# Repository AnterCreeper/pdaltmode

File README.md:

# USB PD Alt-mode Host-side Negotiation

If any questions, welcome for Issues & PRs   
如果有疑问，欢迎提交Issues或PR

**WARNING! This Project is not been fully long-term productive tested and without warranty of any kind, use at your own risk!**   
**警告！该项目未经充分的长期生产环境测试，作者不作任何保证，使用需要你自己衡量**

### License

This project is licensed under the LGPL-2.1-or-later license. **DO NOT** download or clone this project until you have read and agree the LICENSE.     
该项目采用 `LGPL-2.1 以及之后版本` 授权。当你下载或克隆项目时，默认已经阅读并同意该协定。

### TODO

1. Active Cable Support (not in plan)
2. Audio Transmission Function Testing

### Overview

This Project is used to perform PD Logic for Host-side based on the cost-effective (30 cents at the time of writing) WCH CH32X035 32-bit RISC-V microcontroller, to achieve DisplayPort output over Type-C, which can be used on space compact scene.    
该项目基于来自 WCH 的低成本 CH32X035 微控制器，包含了所需的所有主机端的 USB Power Delivery 协议的功能，以实现 Type-C 上 DisplayPort 视频输出功能，可用于 PCB 面积紧凑场景。

Besides, This Project include a validation hardware with GERBER and schematics, 4 layers JLC04081H-3313 Stacking, using TOSHIBA TC358867XBG to convert Video stream from Parallel to DisplayPort Signal.   
此外，该项目附有一个验证硬件，包含 GERBER 和原理图与装配图纸，四层 0.8mm JLC04081H-3313 叠层，采用 TOSHIBA TC358867XBG 将 RGB 并行接口 转换至 DisplayPort 信号输出。

This Project implements state machines defined in:
1. Universal Serial Bus Power Delivery Specification Rev 2.0 Ver 1.3
2. Universal Serial Bus Type-C Cable and Connector Specification Ver 2.2.
3. VESA DisplayPort Alt Mode on USB Type-C Standard. Ver 1.3/1.4.
4. VESA DisplayPort Standard. Version 1, Revision 2.

Doc. 1 and 2 can be accessed from https://github.com/usb-c/USB-Type-C   
For Doc. 3, since **DISTRIBUTION TO NON-MEMBERS IS PROHIBITED**, contact me at [wangzhihao9@hotmail.com](mailto:wangzhihao9@hotmail.com)  
Doc.4 is located at https://glenwing.github.io/docs/DP-1.2.pdf

Datasheet of TC358867XBG is included in the project, which includes external LICENSE.

Some other Specification related to Audio which is needed: (May have copies over web.archive.org)
1. [CEA 861-E](https://members.cta.tech/ctaPublicationDetails/?id=95190170-1031-e811-bbd4-0003ff52999d): A DTV Profile for Uncompressed High Speed Digital Interfaces
2. [IEC60958](https://webstore.iec.ch/en/publication/62829): Digital Audio Interfaces

### Usage

1. Download and Open with MounRiver Studio II [Download Page](http://www.mounriver.com/download)
2. Connect the board with WCH Link-E, then Compile and Run
3. ~~Files except in User is remain unchanged from default.~~

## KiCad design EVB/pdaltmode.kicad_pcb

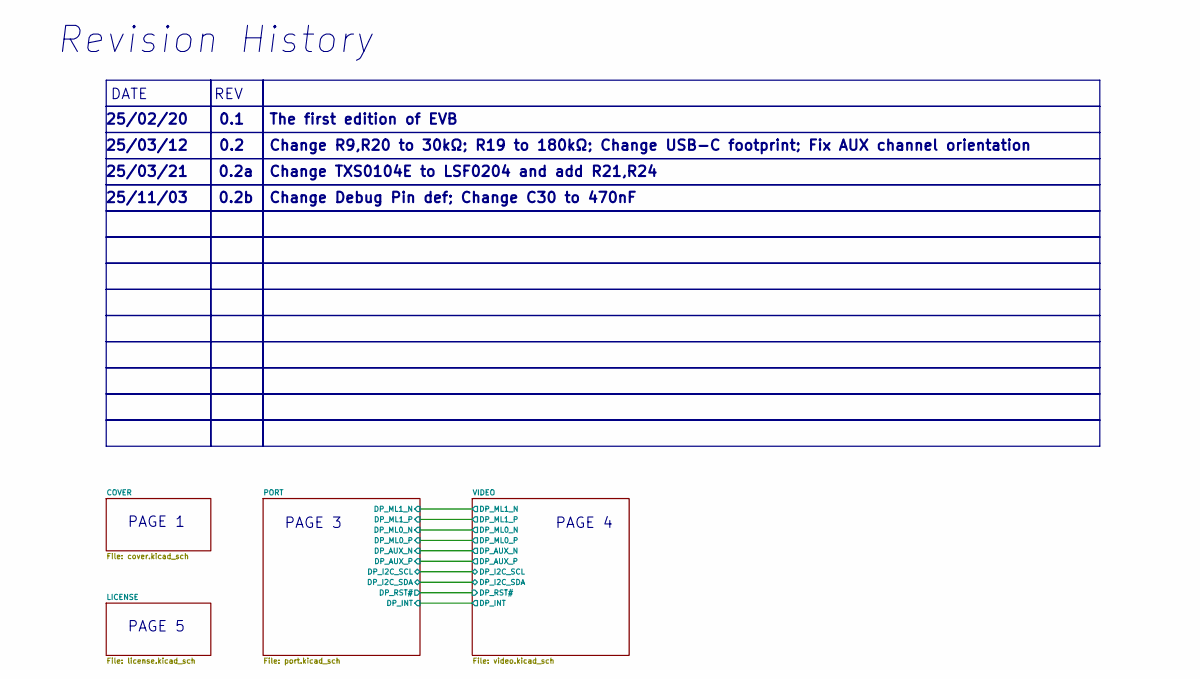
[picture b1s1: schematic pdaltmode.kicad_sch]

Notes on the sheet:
Change Debug Pin def; Change C30 to 470nF
Change TXS0104E to LSF0204 and add R21,R24
PAGE 5
25/11/03
PAGE 3
PAGE 1
0.2b
Change R9,R20 to 30kΩ; R19 to 180kΩ; Change USB-C footprint; Fix AUX channel orientation
0.1
Revision History
The first edition of EVB
DATE
25/03/12
0.2a
0.2
25/03/21
PAGE 4
REV
25/02/20

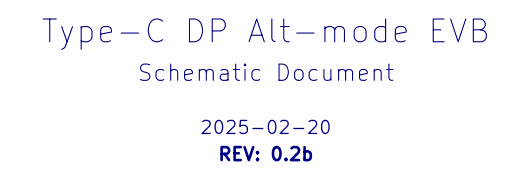
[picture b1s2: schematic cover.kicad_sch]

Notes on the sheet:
REV: 0.2b
2025-02-20
Type-C DP Alt-mode EVB
Schematic Document

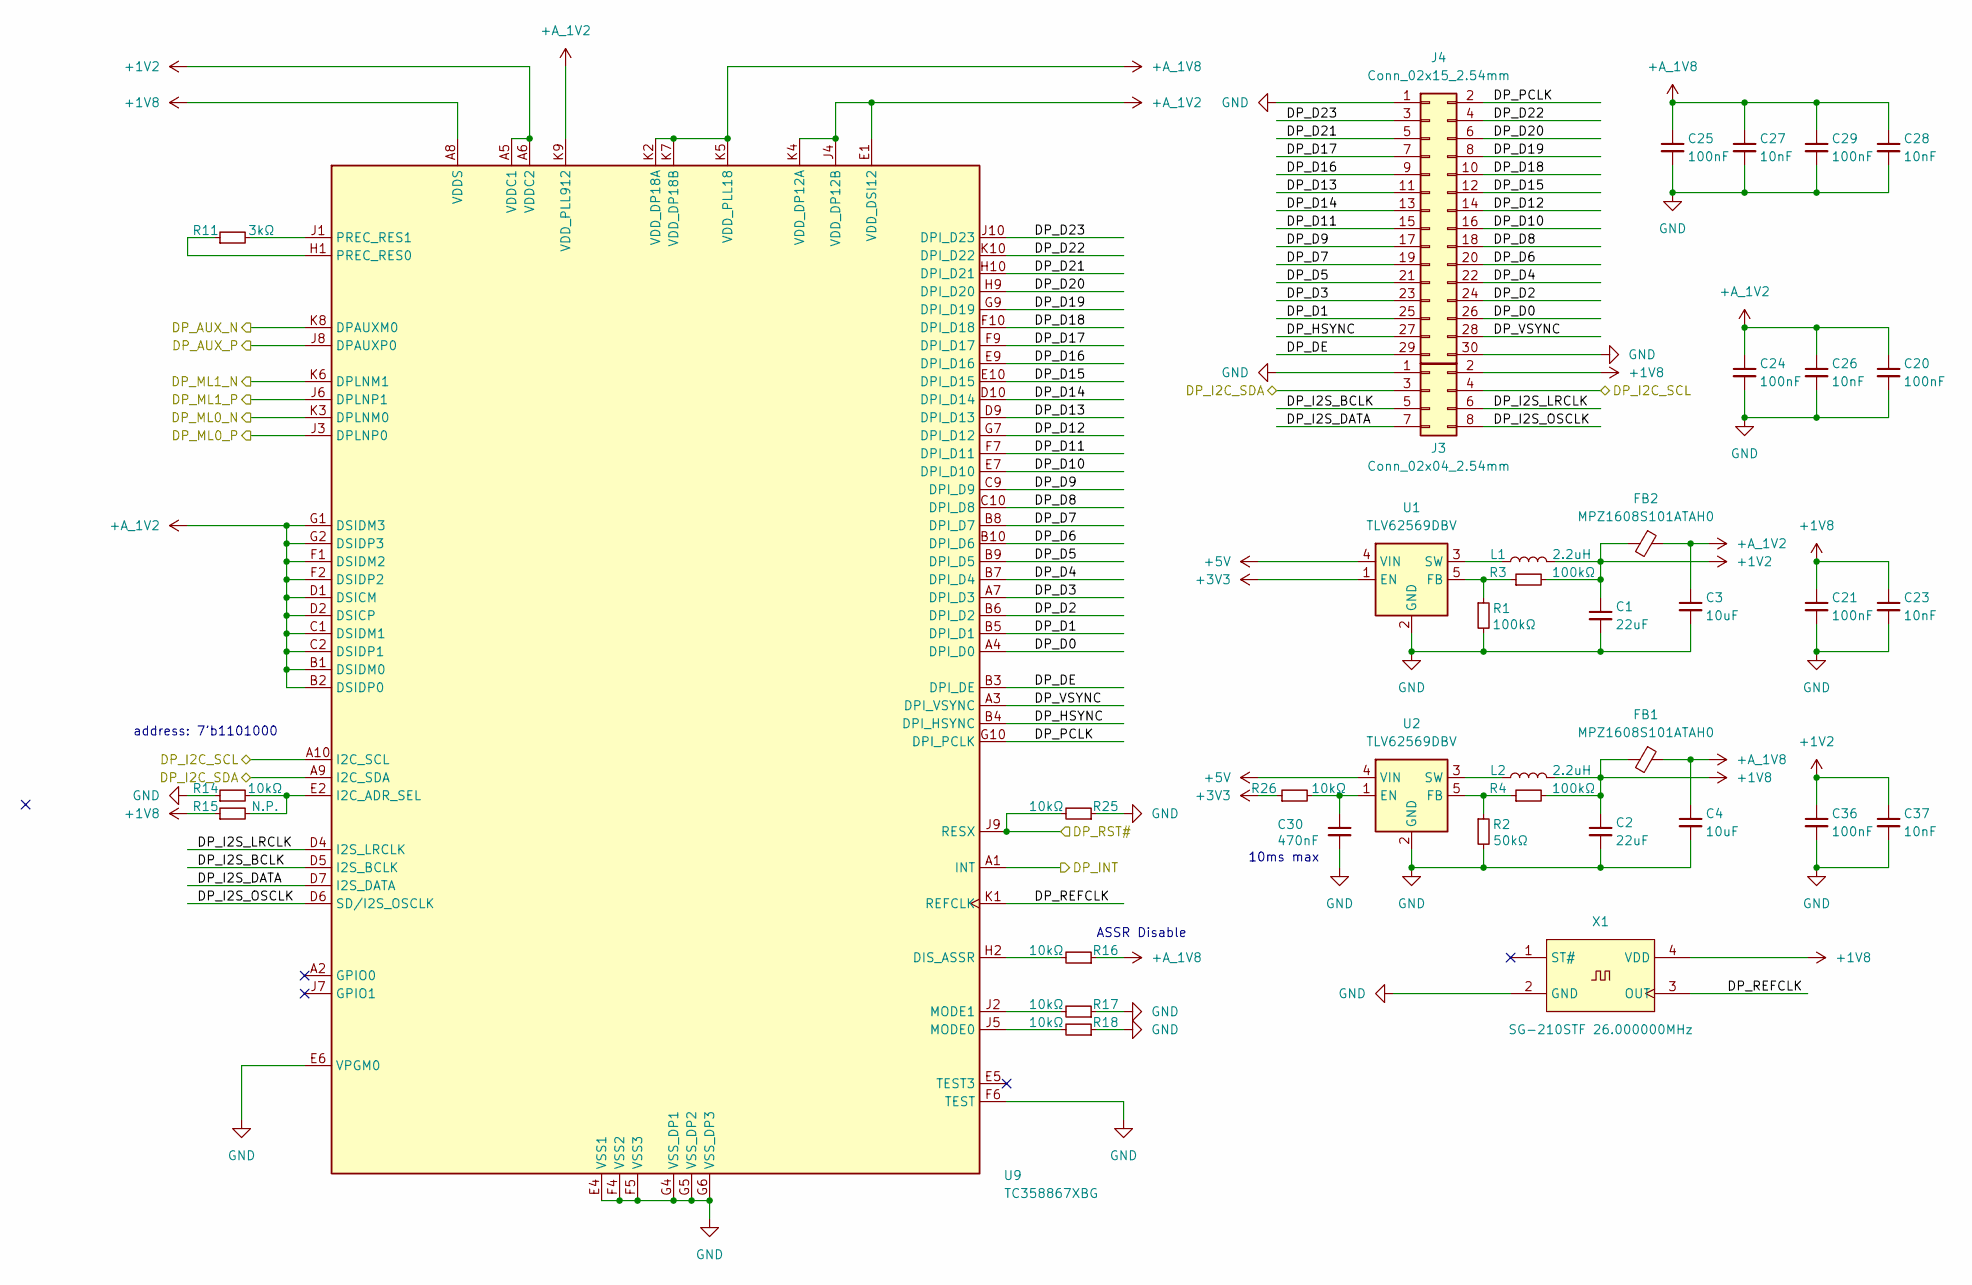
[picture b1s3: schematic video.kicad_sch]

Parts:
C1, C2: 22uF; C_0603_1608Metric
C3, C4: 10uF; C_0603_1608Metric
C20, C21, C24, C25, C29, C36: 100nF; C_0402_1005Metric
C23, C26, C27, C28, C37: 10nF; C_0402_1005Metric
C30: 470nF; C_0402_1005Metric
FB1, FB2: MPZ1608S101ATAH0; L_0603_1608Metric
J3: Conn_02x04_2.54mm; PinHeader_2x04_P2.54mm_Vertical
J4: Conn_02x15_2.54mm; PinHeader_2x15_P2.54mm_Vertical
L1, L2: 2.2uH; L_Murata_DFE201610P
R1, R3, R4: 100kΩ; R_0402_1005Metric
R2: 50kΩ; R_0402_1005Metric
R11: 3kΩ; R_0402_1005Metric
R14, R16, R17, R18, R25, R26: 10kΩ; R_0402_1005Metric
R15: N.P.; R_0402_1005Metric
U1, U2: TLV62569DBV; SOT-23-5
U9: TC358867XBG; Toshiba_VFBGA-80_7.0x7.0mm
X1: SG-210STF 26.000000MHz; Oscillator_SMD_SeikoEpson_SG210-4Pin_2.5x2.0mm

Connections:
+1V2: C1.1, C36.1, C37.1, FB2.2, L1.2, R3.2, U9.A5 (VDDC1), U9.A6 (VDDC2)
+1V8: C2.1, C21.1, C23.1, FB1.2, J3.2, L2.2, R4.2, R15.1, U9.A8 (VDDS), X1.4 (VDD); also elsewhere on the board
+3V3: R26.1, U1.1 (EN); also elsewhere on the board
+5V: U1.4 (VIN), U2.4 (VIN); also elsewhere on the board
+A_1V2: C3.1, C20.1, C24.1, C26.1, FB2.1, U9.B1 (DSIDM0), U9.B2 (DSIDP0), U9.C1 (DSIDM1), U9.C2 (DSIDP1), U9.D1 (DSICM), U9.D2 (DSICP), U9.E1 (VDD_DSI12), U9.F1 (DSIDM2), U9.F2 (DSIDP2), U9.G1 (DSIDM3), U9.G2 (DSIDP3), U9.J4 (VDD_DP12B), U9.K4 (VDD_DP12A), U9.K9 (VDD_PLL912)
+A_1V8: C4.1, C25.1, C27.1, C28.1, C29.1, FB1.1, R16.1, U9.K2 (VDD_DP18A), U9.K5 (VDD_PLL18), U9.K7 (VDD_DP18B)
/PORT/DP_AUX_N: U9.K8 (DPAUXM0); also elsewhere on the board
/PORT/DP_AUX_P: U9.J8 (DPAUXP0); also elsewhere on the board
/PORT/DP_I2C_SCL: J3.4, U9.A10 (I2C_SCL); also elsewhere on the board
/PORT/DP_I2C_SDA: J3.3, U9.A9 (I2C_SDA); also elsewhere on the board
/PORT/DP_INT: U9.A1 (INT); also elsewhere on the board
/PORT/DP_ML0_N: U9.K3 (DPLNM0); also elsewhere on the board
/PORT/DP_ML0_P: U9.J3 (DPLNP0); also elsewhere on the board
/PORT/DP_ML1_N: U9.K6 (DPLNM1); also elsewhere on the board
/PORT/DP_ML1_P: U9.J6 (DPLNP1); also elsewhere on the board
/PORT/DP_RST#: R25.2, U9.J9 (RESX); also elsewhere on the board
/VIDEO/DP_D0: J4.26, U9.A4 (DPI_D0)
/VIDEO/DP_D1: J4.25, U9.B5 (DPI_D1)
/VIDEO/DP_D2: J4.24, U9.B6 (DPI_D2)
/VIDEO/DP_D3: J4.23, U9.A7 (DPI_D3)
/VIDEO/DP_D4: J4.22, U9.B7 (DPI_D4)
/VIDEO/DP_D5: J4.21, U9.B9 (DPI_D5)
/VIDEO/DP_D6: J4.20, U9.B10 (DPI_D6)
/VIDEO/DP_D7: J4.19, U9.B8 (DPI_D7)
/VIDEO/DP_D8: J4.18, U9.C10 (DPI_D8)
/VIDEO/DP_D9: J4.17, U9.C9 (DPI_D9)
/VIDEO/DP_D10: J4.16, U9.E7 (DPI_D10)
/VIDEO/DP_D11: J4.15, U9.F7 (DPI_D11)
/VIDEO/DP_D12: J4.14, U9.G7 (DPI_D12)
/VIDEO/DP_D13: J4.11, U9.D9 (DPI_D13)
/VIDEO/DP_D14: J4.13, U9.D10 (DPI_D14)
/VIDEO/DP_D15: J4.12, U9.E10 (DPI_D15)
/VIDEO/DP_D16: J4.9, U9.E9 (DPI_D16)
/VIDEO/DP_D17: J4.7, U9.F9 (DPI_D17)
/VIDEO/DP_D18: J4.10, U9.F10 (DPI_D18)
/VIDEO/DP_D19: J4.8, U9.G9 (DPI_D19)
/VIDEO/DP_D20: J4.6, U9.H9 (DPI_D20)
/VIDEO/DP_D21: J4.5, U9.H10 (DPI_D21)
/VIDEO/DP_D22: J4.4, U9.K10 (DPI_D22)
/VIDEO/DP_D23: J4.3, U9.J10 (DPI_D23)
/VIDEO/DP_DE: J4.29, U9.B3 (DPI_DE)
/VIDEO/DP_HSYNC: J4.27, U9.B4 (DPI_HSYNC)
/VIDEO/DP_I2S_BCLK: J3.5, U9.D5 (I2S_BCLK)
/VIDEO/DP_I2S_DATA: J3.7, U9.D7 (I2S_DATA)
/VIDEO/DP_I2S_LRCLK: J3.6, U9.D4 (I2S_LRCLK)
/VIDEO/DP_I2S_OSCLK: J3.8, U9.D6 (SD/I2S_OSCLK)
/VIDEO/DP_PCLK: J4.2, U9.G10 (DPI_PCLK)
/VIDEO/DP_REFCLK: U9.K1 (REFCLK), X1.3 (OUT)
/VIDEO/DP_VSYNC: J4.28, U9.A3 (DPI_VSYNC)
GND: C1.2, C2.2, C3.2, C4.2, C20.2, C21.2, C23.2, C24.2, C25.2, C26.2, C27.2, C28.2, C29.2, C30.2, C36.2, C37.2, J3.1, J4.1, J4.30, R1.2, R2.2, R14.1, R17.1, R18.1, R25.1, U1.2 (GND), U2.2 (GND), U9.E4 (VSS1), U9.E6 (VPGM0), U9.F4 (VSS2), U9.F5 (VSS3), U9.F6 (TEST), U9.G4 (VSS_DP1), U9.G5 (VSS_DP2), U9.G6 (VSS_DP3), X1.2 (GND); also elsewhere on the board
unnamed: R1.1, R3.1, U1.5 (FB)
unnamed: L1.1, U1.3 (SW)
unnamed: C30.1, R26.2, U2.1 (EN)
unnamed: R2.1, R4.1, U2.5 (FB)
unnamed: L2.1, U2.3 (SW)
unnamed: R16.2, U9.H2 (DIS_ASSR)
unnamed: R14.2, R15.2, U9.E2 (I2C_ADR_SEL)
unnamed: R18.2, U9.J5 (MODE0)
unnamed: R17.2, U9.J2 (MODE1)
unnamed: R11.1, U9.H1 (PREC_RES0)
unnamed: R11.2, U9.J1 (PREC_RES1)

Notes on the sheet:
ASSR Disable
10ms max
address: 7'b1101000

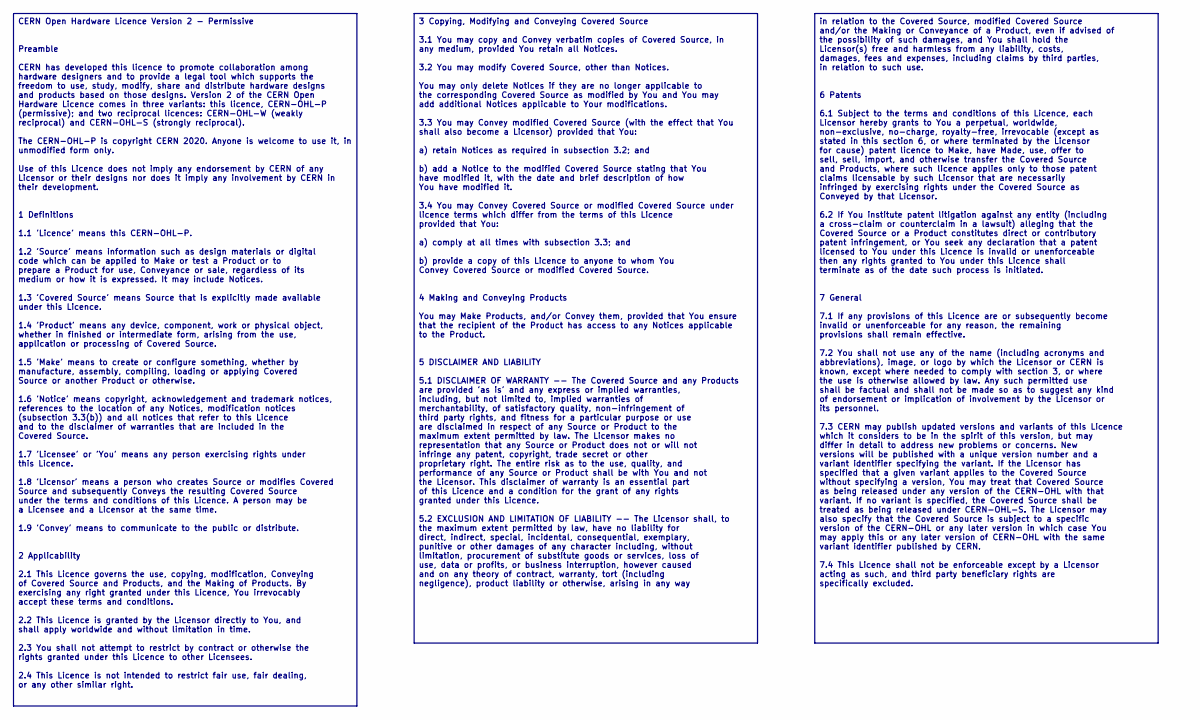
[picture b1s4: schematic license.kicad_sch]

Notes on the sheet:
3 Copying, Modifying and Conveying Covered Source 3.1 You may copy and Convey verbatim copies of Covered Source, in any medium, provided You retain all Notices. 3.2 You may modify Covered Source, other than Notices. You may only delete Notices if they are no longer applicable to the corresponding C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
CERN Open Hardware Licence Version 2 - Permissive Preamble CERN has developed this licence to promote collaboration among hardware designers and to provide a legal tool which supports the freedom to use, study, modify, share and distribute hardware designs and products based on those designs. Versi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
in relation to the Covered Source, modified Covered Source and/or the Making or Conveyance of a Product, even if advised of the possibility of such damages, and You shall hold the Licensor(s) free and harmless from any liability, costs, damages, fees and expenses, including claims by third parties,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

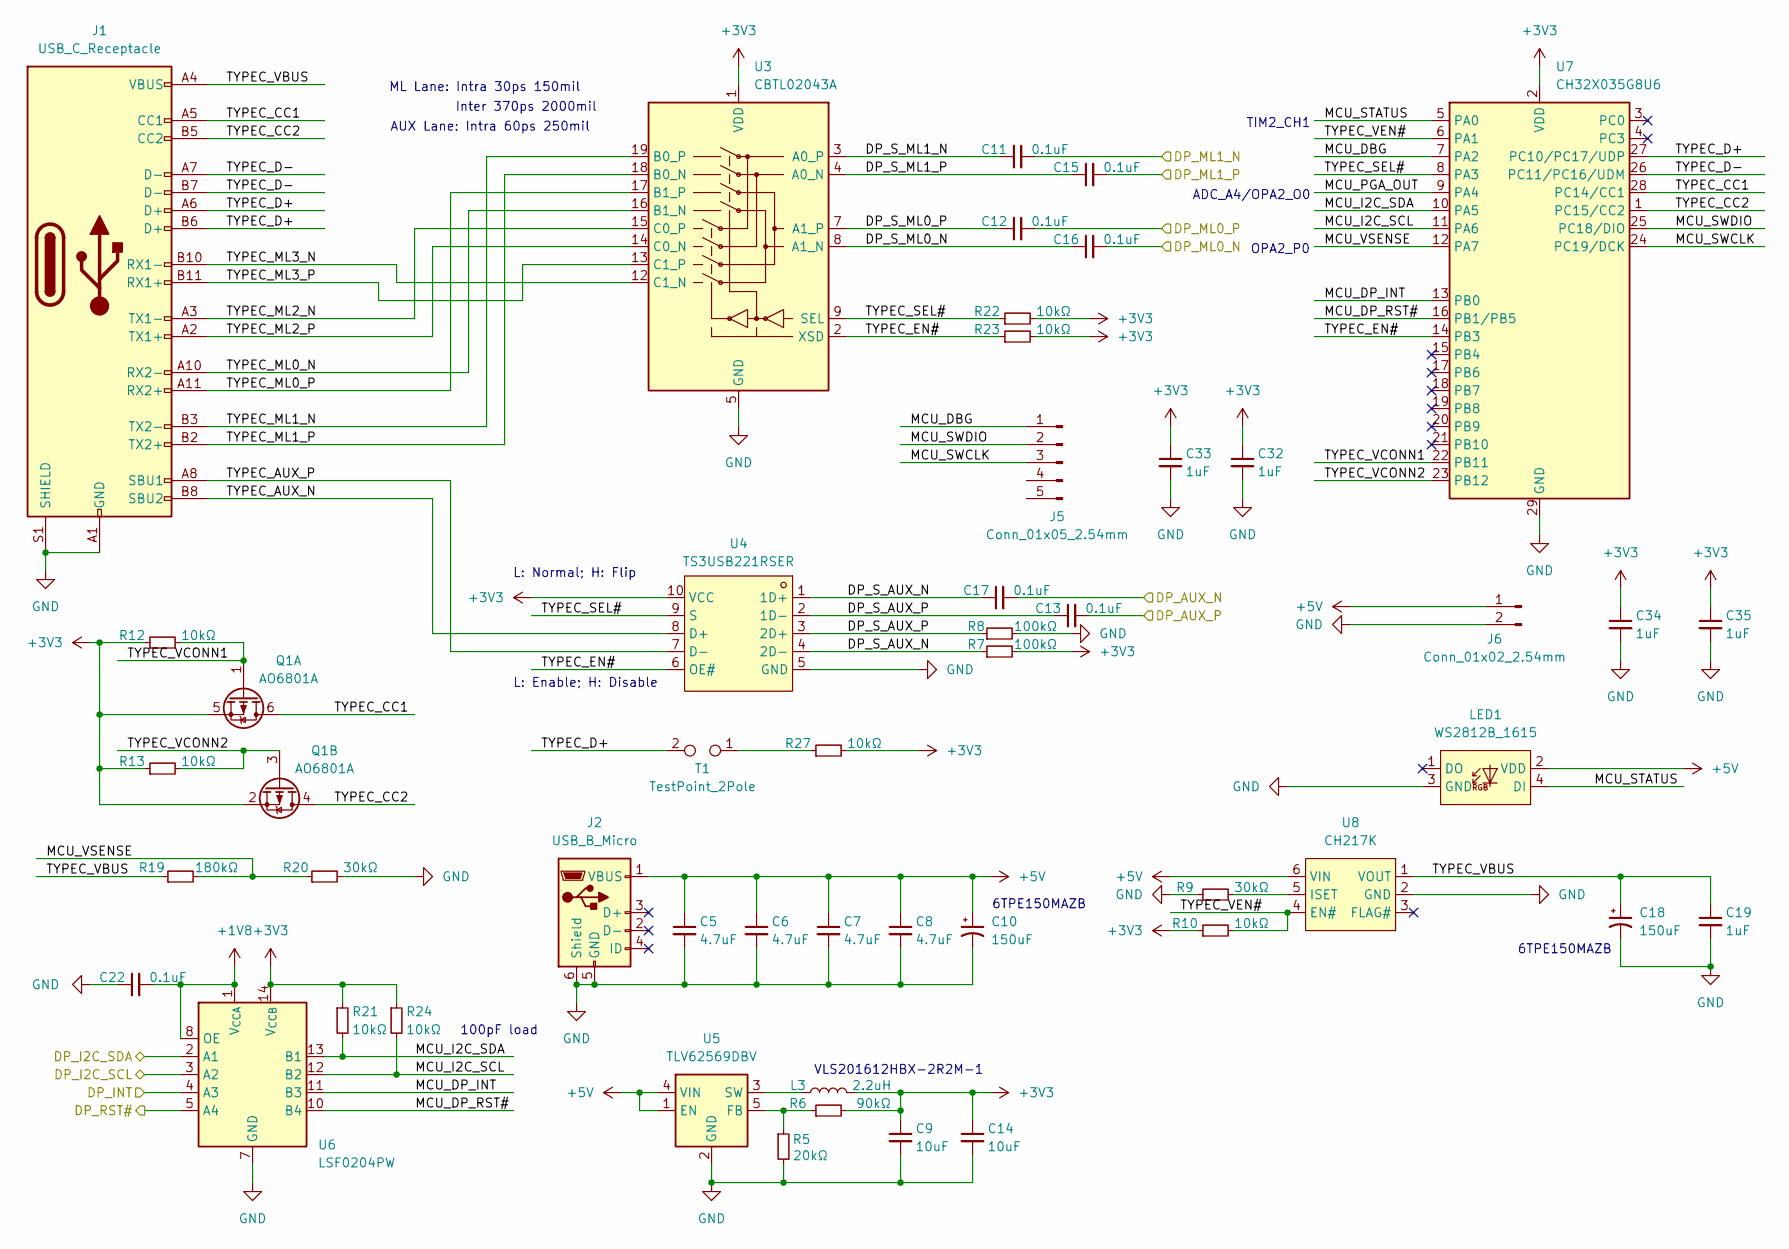
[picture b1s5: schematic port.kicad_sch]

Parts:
C5, C6, C7, C8: 4.7uF; C_0603_1608Metric
C9, C14: 10uF; C_0603_1608Metric
C10, C18: 150uF; CP_EIA-3528-21_Kemet-B
C11, C12, C15, C16: 0.1uF; C_0201_0603Metric
C13, C17, C22: 0.1uF; C_0402_1005Metric
C19, C32, C33, C34, C35: 1uF; C_0402_1005Metric
J1: USB_C_Receptacle; USB_C_Receptacle_Amphenol_10137062-00021LF
J2: USB_B_Micro; USB_Mini-B_Wuerth_651005136521
J5: Conn_01x05_2.54mm; PinHeader_1x05_P2.54mm_Vertical
J6: Conn_01x02_2.54mm; PinHeader_1x02_P2.54mm_Vertical
L3: 2.2uH; L_Murata_DFE201610P
LED1: WS2812B_1615; LED_WS2812B-1615_SMD-4P_1.6x1.5mm; LCSC Part Name XL-1615RGBC-WS2812B-S
Q1: AO6801A; SOT-23-6
R5: 20kΩ; R_0402_1005Metric
R6: 90kΩ; R_0402_1005Metric
R7, R8: 100kΩ; R_0402_1005Metric
R9, R20: 30kΩ; R_0402_1005Metric
R10, R12, R13, R21, R22, R23, R24, R27: 10kΩ; R_0402_1005Metric
R19: 180kΩ; R_0402_1005Metric
T1: TestPoint_2Pole; TestPoint_Bridge_Pitch2.0mm_Drill0.7mm
U3: CBTL02043A; WQFN-20-1EP_2.5x4.5mm_P0.5mm_EP1x2.9mm
U4: TS3USB221RSER; Texas_UQFN-10_1.5x2mm_P0.5mm
U5: TLV62569DBV; SOT-23-5
U6: LSF0204PW; TSSOP-14_4.4x5mm_P0.65mm
U7: CH32X035G8U6; QFN-28-1EP_4x4mm_P0.4mm_EP2.7x2.7mm
U8: CH217K; SOT-23-6

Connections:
+1V8: C22.2, U6.1 (V_{CCA}), U6.8 (OE); also elsewhere on the board
+3V3: C9.1, C14.1, C32.1, C33.1, C34.1, C35.1, L3.2, Q1.2 (S), Q1.5 (S), R6.2, R7.2, R10.1, R12.1, R13.1, R21.1, R22.2, R23.2, R24.1, R27.2, U3.1 (VDD), U3.6 (VDD), U3.10 (VDD), U4.10 (VCC), U6.14 (V_{CCB}), U7.2 (VDD); also elsewhere on the board
+5V: C5.1, C6.1, C7.1, C8.1, C10.1, J2.1 (VBUS), J6.1, LED1.2 (VDD), U5.1 (EN), U5.4 (VIN), U8.6 (VIN); also elsewhere on the board
/PORT/DP_AUX_N: C17.2; also elsewhere on the board
/PORT/DP_AUX_P: C13.2; also elsewhere on the board
/PORT/DP_I2C_SCL: U6.3 (A2); also elsewhere on the board
/PORT/DP_I2C_SDA: U6.2 (A1); also elsewhere on the board
/PORT/DP_INT: U6.4 (A3); also elsewhere on the board
/PORT/DP_ML0_N: C16.2; also elsewhere on the board
/PORT/DP_ML0_P: C12.2; also elsewhere on the board
/PORT/DP_ML1_N: C11.2; also elsewhere on the board
/PORT/DP_ML1_P: C15.2; also elsewhere on the board
/PORT/DP_RST#: U6.5 (A4); also elsewhere on the board
/PORT/DP_S_AUX_N: C17.1, R7.1, U4.1 (1D+), U4.4 (2D-)
/PORT/DP_S_AUX_P: C13.1, R8.1, U4.2 (1D-), U4.3 (2D+)
/PORT/DP_S_ML0_N: C16.1, U3.8 (A1_N)
/PORT/DP_S_ML0_P: C12.1, U3.7 (A1_P)
/PORT/DP_S_ML1_N: C11.1, U3.3 (A0_P)
/PORT/DP_S_ML1_P: C15.1, U3.4 (A0_N)
/PORT/MCU_DBG: J5.1, U7.7 (PA2)
/PORT/MCU_DP_INT: U6.11 (B3), U7.13 (PB0)
/PORT/MCU_DP_RST#: U6.10 (B4), U7.16 (PB1/PB5)
/PORT/MCU_I2C_SCL: R24.2, U6.12 (B2), U7.11 (PA6)
/PORT/MCU_I2C_SDA: R21.2, U6.13 (B1), U7.10 (PA5)
/PORT/MCU_PGA_OUT: U7.9 (PA4)
/PORT/MCU_STATUS: LED1.4 (DI), U7.5 (PA0)
/PORT/MCU_SWCLK: J5.3, U7.24 (PC19/DCK)
/PORT/MCU_SWDIO: J5.2, U7.25 (PC18/DIO)
/PORT/MCU_VSENSE: R19.2, R20.1, U7.12 (PA7)
/PORT/TYPEC_AUX_N: J1.B8 (SBU2), U4.8 (D+)
/PORT/TYPEC_AUX_P: J1.A8 (SBU1), U4.7 (D-)
/PORT/TYPEC_CC1: J1.A5 (CC1), Q1.6 (D), U7.28 (PC14/CC1)
/PORT/TYPEC_CC2: J1.B5 (CC2), Q1.4 (D), U7.1 (PC15/CC2)
/PORT/TYPEC_D+: J1.A6 (D+), J1.B6 (D+), T1.2, U7.27 (PC10/PC17/UDP)
/PORT/TYPEC_D-: J1.A7 (D-), J1.B7 (D-), U7.26 (PC11/PC16/UDM)
/PORT/TYPEC_EN#: R23.1, U3.2 (XSD), U4.6 (OE#), U7.14 (PB3)
/PORT/TYPEC_ML0_N: J1.A10 (RX2-), U3.16 (B1_N)
/PORT/TYPEC_ML0_P: J1.A11 (RX2+), U3.17 (B1_P)
/PORT/TYPEC_ML1_N: J1.B3 (TX2-), U3.19 (B0_P)
/PORT/TYPEC_ML1_P: J1.B2 (TX2+), U3.18 (B0_N)
/PORT/TYPEC_ML2_N: J1.A3 (TX1-), U3.15 (C0_P)
/PORT/TYPEC_ML2_P: J1.A2 (TX1+), U3.14 (C0_N)
/PORT/TYPEC_ML3_N: J1.B10 (RX1-), U3.12 (C1_N)
/PORT/TYPEC_ML3_P: J1.B11 (RX1+), U3.13 (C1_P)
/PORT/TYPEC_SEL#: R22.1, U3.9 (SEL), U4.9 (S), U7.8 (PA3)
/PORT/TYPEC_VBUS: C18.1, C19.1, J1.A4 (VBUS), J1.A9 (VBUS), J1.B4 (VBUS), J1.B9 (VBUS), R19.1, U8.1 (VOUT)
/PORT/TYPEC_VCONN1: Q1.1 (G), R12.2, U7.22 (PB11)
/PORT/TYPEC_VCONN2: Q1.3 (G), R13.2, U7.23 (PB12)
/PORT/TYPEC_VEN#: R10.2, U7.6 (PA1), U8.4 (EN#)
GND: C5.2, C6.2, C7.2, C8.2, C9.2, C10.2, C14.2, C18.2, C19.2, C22.1, C32.2, C33.2, C34.2, C35.2, J1.A1 (GND), J1.A12 (GND), J1.B1 (GND), J1.B12 (GND), J1.S1 (SHIELD), J2.5 (GND), J2.6 (Shield), J6.2, LED1.3 (GND), R5.2, R8.2, R9.1, R20.2, U3.5 (GND), U3.11 (GND), U3.20 (GND), U3.21 (GND), U4.5 (GND), U5.2 (GND), U6.7 (GND), U7.29 (GND), U8.2 (GND); also elsewhere on the board
unnamed: R27.1, T1.1
unnamed: R5.1, R6.1, U5.5 (FB)
unnamed: L3.1, U5.3 (SW)
unnamed: R9.2, U8.5 (ISET)

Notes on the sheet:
TIM2_CH1
6TPE150MAZB
AUX Lane: Intra 60ps 250mil
VLS201612HBX-2R2M-1
Inter 370ps 2000mil
OPA2_P0
100pF load
L: Enable; H: Disable
ADC_A4/OPA2_O0
ML Lane: Intra 30ps 150mil
L: Normal; H: Flip

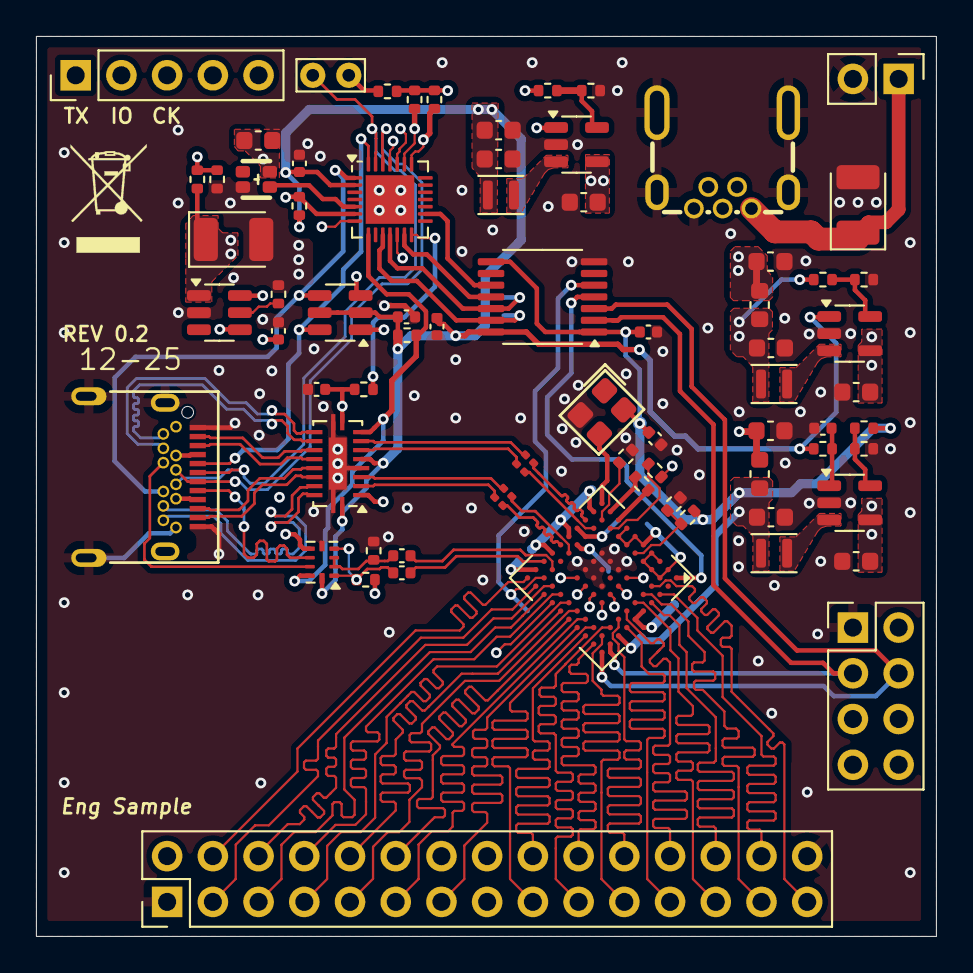
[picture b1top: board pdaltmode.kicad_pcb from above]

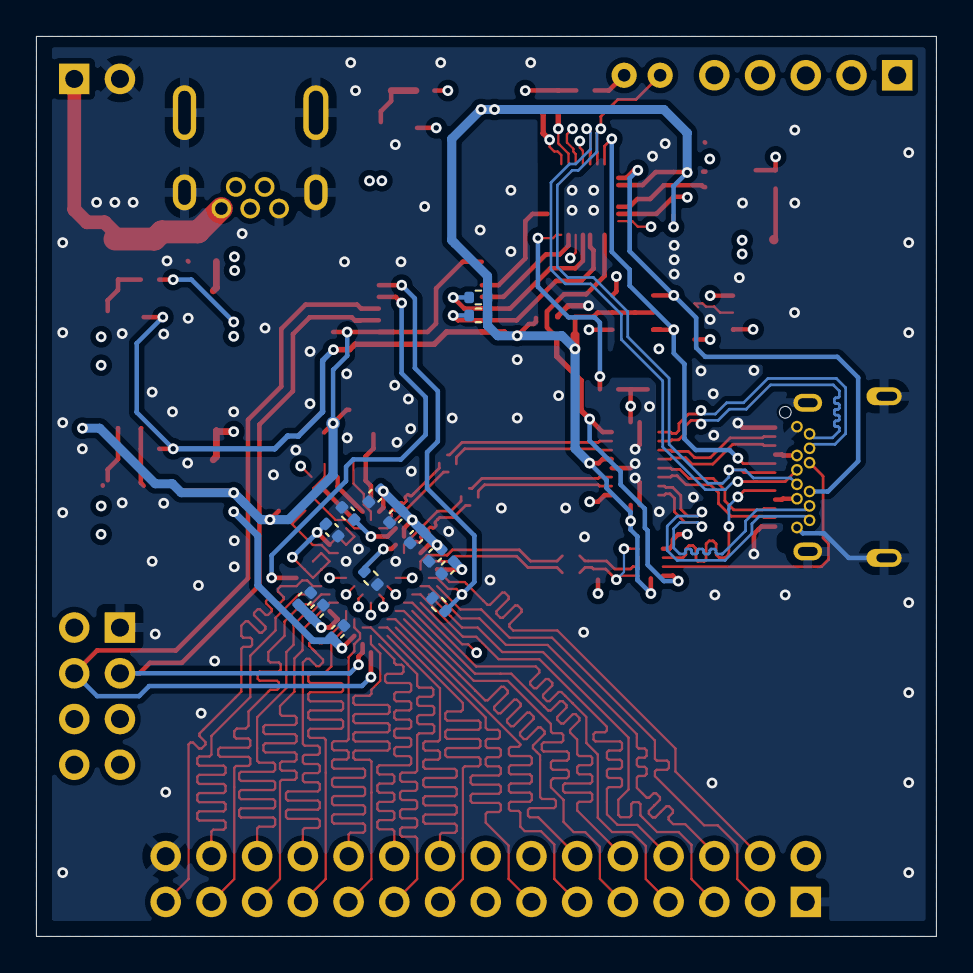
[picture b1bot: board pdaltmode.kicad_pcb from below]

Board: 4 copper layers, 50.0 x 50.0 mm, 87 parts (14 on the bottom side), 100 nets.

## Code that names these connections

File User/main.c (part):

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
void GPIO_Toggle_INIT() {
    RCC_APB2PeriphClockCmd(RCC_APB2Periph_GPIOA, ENABLE);
    GPIO_OUT_INIT(GPIOA, GPIO_Pin_1, Bit_SET); //TYPEC_VEN#
    GPIO_OUT_INIT(GPIOA, GPIO_Pin_3, Bit_SET); //TYPEC_SEL#

    RCC_APB2PeriphClockCmd(RCC_APB2Periph_GPIOB, ENABLE);
    GPIO_OUT_INIT(GPIOB, GPIO_Pin_3, Bit_SET); //TYPEC_EN#
    GPIO_OUT_INIT(GPIOB, GPIO_Pin_11, Bit_SET); //TYPEC_VCONN1
    GPIO_OUT_INIT(GPIOB, GPIO_Pin_12, Bit_SET); //TYPEC_VCONN2

    printf("Enable GPIO\r\n");
    return;
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void GPIO_Toggle_VCONN(int state){
    printf("Toggle VCONN %s\r\n", state > 0 ? "ON" : "OFF");
    if(state > 2) assert("Bad VCONN Toggle Pin");
    GPIO_WriteBit(GPIOB, GPIO_Pin_11, state & 0x2 ? Bit_RESET : Bit_SET); //TYPEC_VCONN1
    GPIO_WriteBit(GPIOB, GPIO_Pin_12, state & 0x1 ? Bit_RESET : Bit_SET); //TYPEC_VCONN2
    return;
}

void GPIO_Toggle_DPSEL(int state){
    int sel = state ^ ((USBPD->CONFIG & CC_SEL) > 0);
    printf("Toggle DP MUX %s\r\n", sel ? "Flip" : "Normal");
    GPIO_WriteBit(GPIOA, GPIO_Pin_3, sel); //TYPEC_SEL#
    return;
}

void GPIO_Toggle_DPSIG(int state){
    printf("Toggle DP SIGNAL %s\r\n", state ? "ON" : "OFF");
    GPIO_WriteBit(GPIOB, GPIO_Pin_3, state ? Bit_RESET : Bit_SET); //TYPEC_EN#
    return;
}

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
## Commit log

2025-02-15 fix some known issues.
2025-02-20 modified debug options.
2025-02-22 fix typo.
2025-02-23 add default files.
2025-03-03 submit EVB PCB project.
2025-03-03 add TC358867XBG datasheet.
2025-03-03 add assembly pdf.
2025-03-03 add preview pic.
2025-03-04 DFM ECO.
2025-03-04 Sigrity ECO.
2025-03-12 update v0.2.
2025-03-13 update mcu firmware.
2025-03-13 fix known issues.
2025-03-14 minor version update.
2025-03-14 update.
2025-03-15 add .gitignore
2025-03-17 clean useless file.
2025-03-17 remove kicad_prl file.
2025-03-19 cleaning code.
2025-03-19 clean header include
2025-03-20 upload 3d step model
2025-03-20 update USB-C step model
2025-03-22 update evb pcb files.
2025-03-22 tiny gerber ECO
2025-03-23 update to standard USB footprint, and 0.2a revision PCB.
2025-03-30 update MPD logic.
2025-03-30 clean.
2025-03-30 update mpd
2025-03-31 update macro for reg
2025-06-29 update files.
2025-06-29 remove MPD_IIC_DBG macro.
2025-08-19 fix bugs.
2025-09-02 tons of updates.
2025-09-04 add support for audio.
2025-09-05 bug fixed, release version.
2025-09-18 add issue template.
2025-11-03 update EVB.
2025-11-03 clean codes.
2025-11-05 faster bit field extract, using sll+srl.
2025-11-24 update README.
2025-12-08 update schematic pdf.(however gerber and assembly are not.)
2025-12-08 remove unused empty file.
2025-12-10 typo fix.
2025-12-24 tiny fixup.
2025-12-31 update preview photo and stack info.
2026-01-12 system info update.

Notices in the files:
EVB/license.kicad_sch:
granted under this Licence.
Hardware Licence comes in three variants: this licence, CERN-OHL-P
(permissive); and two reciprocal licences: CERN-OHL-W (weakly
reciprocal) and CERN-OHL-S (strongly reciprocal).
The CERN-OHL-P is copyright CERN 2020. Anyone is welcome to use it, in
1.1 'Licence' means this CERN-OHL-P.
under the terms and conditions of this Licence. A person may be
of Covered Source and Products, and the Making of Products. By
exercising any right granted under this Licence, You irrevocably
licensed to You under this Licence is invalid or unenforceable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
